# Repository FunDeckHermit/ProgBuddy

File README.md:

# ProgBuddy

ProgBuddy is a compact USB 2.0 hub and power-monitoring board designed for practical bench use and embedded USB debugging. It combines a high-side current sensing front end, USB PD passthrough switching, a web interface over USB CDC/NCM, and a small user-facing display for live system status.

## Features

- USB 2.0 hub function with configurable upstream/downstream swap capability
- Accurate current sensing for downstream ports and total hub current
- INA229-based voltage and energy monitoring
- USB PD passthrough with CC-line switching and port control
- Web interface exposed over USB communication device class (CDC/NCM)
- LCD display for live voltages, power, and status information
- Flexible board layout for USB upstream/downstream swapping and reconfiguration

## Design goals

This project is intended to make USB power and debugging data visible and controllable in a single tool. The board is useful for:

- measuring real-time current draw from USB devices
- validating USB PD behavior and pass-through routing
- monitoring port voltage and energy usage
- debugging USB device behavior from a simple web dashboard
- presenting live status on a local panel without needing a separate host tool

## Hardware overview

The system integrates several key functions:

- USB 2.0 hub switching and port routing
- accurate current measurement using dedicated sensing hardware
- bus voltage and energy calculations with the INA229
- USB-C PD passthrough handling with CC switching
- configurable USB upstream/downstream connection options
- local display and status indication

## Firmware and interface

The project exposes a browser-based interface over USB CDC/NCM, allowing inspection and control without a traditional serial adapter stack. This makes it convenient for lab, prototype, and dev-board workflows where a clean USB-connected control path is valuable.

## Typical use cases

- USB port power auditing
- USB device validation and debugging
- PD-aware hub testing
- Bench monitoring for USB-powered electronics
- Controlled power and signal routing in prototypes

## Notes

This repository contains the design files and project documentation for the hardware and embedded firmware work. The board is intended to be configurable and practical, with emphasis on measurement accuracy, USB signal integrity, and operational flexibility.

## Status

This project is an active hardware and firmware design, with emphasis on USB hub functionality, power monitoring, and USB PD passthrough behavior.

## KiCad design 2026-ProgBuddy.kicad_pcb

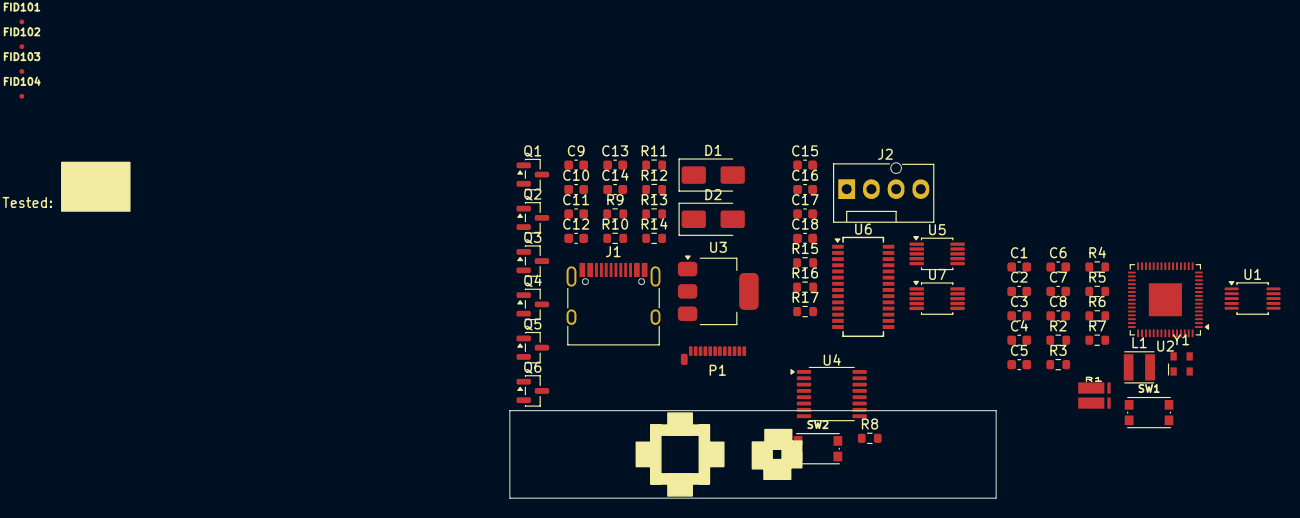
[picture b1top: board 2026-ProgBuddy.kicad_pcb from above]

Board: 4 copper layers, 50.0 x 9.0 mm, 61 parts (0 on the bottom side), 55 nets, no tracks yet.

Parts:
C1, C2, C11, C14: 100nF; C_0603_1608Metric
C3, C4, C5, C6, C7, C8, C9, C10, C12, C13, C15, C16, C17, C18: 2.2uF; C_0603_1608Metric
D1, D2: SS14; D_SMA
FID101, FID102, FID103, FID104: Fiducial; Fiducial_0.5mm_Mask1mm
J1: UJ20-C-H-C-4-SMT-TR; USB_C_Receptacle_SSKY_UJ20-C-H-C-4-SMT-TR
J2: Conn_01x04; FanPinHeader_1x04_P2.54mm_Vertical
L1: 3.3uH; L_Bourns-3015
P1: USB_C_Plug; USB_C_Plug_Molex_105444
Q1, Q2, Q4, Q6: Si2347DS; SOT-23
Q3, Q5: BSS316; SOT-23
R1: 33mR; R_Shunt_Susumu_1206
R2, R3: 68R; R_0603_1608Metric
R4, R5, R6: 33R; R_0603_1608Metric
R7, R8: 1K0; R_0603_1608Metric
R9, R10, R11, R12: 10K; R_0603_1608Metric
R13, R14: 5K1; R_0603_1608Metric
R15, R16, R17: 2K7; R_0603_1608Metric
SW1, SW2: KMR223GLFG; SW_Push_1P1T_NO_CK_KMR2
U1: INA229; TSSOP-10_3x3mm_P0.5mm
U2: RP2354A; QFN-60-1EP_7x7mm_P0.4mm_EP3.4x3.4mm
U3: TLV1117-33CDCYG3; SOT-223-3_TabPin2
U4: HEF4052BTT; TSSOP-16_4.4x5mm_P0.65mm
U5, U7: FSUSB42MUX; MSOP-10_3x3mm_P0.5mm
U6: FE1.1s; SSOP-28_3.9x9.9mm_P0.635mm
Y1: ASDMB-12.000MHz; Oscillator_SMD_Abracon_ASDMB-4Pin_2.5x2.0mm

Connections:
12MHz: U2.21 (XIN), U6.3 (XIN), Y1.3 (Out)
+1V1: C7.1, C8.1, L1.2, U2.6 (DVDD), U2.23 (DVDD), U2.39 (DVDD), U2.50 (VREG_FB)
+1V8: C17.1, C18.1, U6.12 (VD18_O), U6.28 (VD18)
+3.3V: C2.1, C5.1, C6.1, C12.1, C13.1, C14.1, C15.1, C16.1, R4.1, R16.1, R17.1, U1.6 (VS), U2.1 (IOVDD), U2.11 (IOVDD), U2.20 (IOVDD), U2.30 (IOVDD), U2.38 (IOVDD), U2.44 (ADC_AVDD), U2.45 (IOVDD), U2.49 (VREG_VIN), U2.53 (USB_OTP_VDD), U2.54 (QSPI_IOVDD), U3.2 (VO), U4.11 (1Y3), U5.1 (VCC), U6.13 (VD33), U6.18 (VBUSM), U6.19 (BUSJ), U6.21 (VD33_O), U7.1 (VCC), Y1.4 (VDD)
+5C: D2.2 (A), P1.A4 (VBUS), P1.A9 (VBUS), P1.B4 (VBUS), P1.B9 (VBUS), Q2.3 (D), U4.15 (1Y2)
+5F: D1.2 (A), J1.A4 (VBUS), J1.A9 (VBUS), J1.B4 (VBUS), J1.B9 (VBUS), Q4.3 (D), U4.14 (1Y1)
+5VD: C9.1, C10.1, C11.1, D1.1 (K), D2.1 (K), U3.3 (VI), U4.6 (~E), U4.16 (VDD)
D+_{1}: J1.A6 (D+), J1.B6 (D+), U5.9 (HSD2+), U7.9 (HSD2+)
D+_{2}: P1.A6 (D+), U5.7 (HSD1+), U7.7 (HSD1+)
D-_{1}: J1.A7 (D-), J1.B7 (D-), U5.8 (HSD2-), U7.8 (HSD2-)
D-_{2}: P1.A7 (D-), U5.6 (HSD1-), U7.6 (HSD1-)
EN_Down: Q3.1 (G), R10.1, U2.27 (GPIO16)
EN_Up: Q5.1 (G), R11.1, U2.28 (GPIO17)
GND: C2.2, C3.2, C4.2, C5.2, C6.2, C7.2, C8.2, C9.2, C10.2, C11.2, C12.2, C13.2, C14.2, C15.2, C16.2, C17.2, C18.2, J1.A1 (GND), J1.A12 (GND), J1.B1 (GND), J1.B12 (GND), J1.S1 (SHIELD), J2.4, P1.A1 (GND), P1.A12 (GND), P1.B1 (GND), P1.B12 (GND), P1.SH (SHIELD), Q3.2 (S), Q5.2 (S), R7.2, R8.2, R10.2, R11.2, R13.2, R14.2, R15.2, U1.1 (~CS), U1.7 (GND), U2.47 (VREG_PGND), U2.61 (GND), U3.1 (GND), U4.7 (VEE), U4.8 (VSS), U5.5 (GND), U6.1 (VSS), U7.5 (GND), Y1.2 (GND)
unnamed: J1.A5 (CC1), R14.1
unnamed: J1.B5 (CC2), R13.1
unnamed: J2.2, U6.7 (DP3)
unnamed: J2.3, U6.6 (DM3)
unnamed: Q1.3 (D), R1.1
unnamed: Q1.1 (G), Q2.1 (G), Q3.3 (D), R9.2
unnamed: Q1.2 (S), Q2.2 (S), R9.1
unnamed: Q4.1 (G), Q5.3 (D), Q6.1 (G), R12.2
unnamed: Q4.2 (S), Q6.2 (S), R12.1
unnamed: Q6.3 (D), R1.4
unnamed: R7.1, SW1.1
unnamed: R8.1, SW2.1
unnamed: C1.1, R3.2, U1.10 (IN+)
unnamed: C1.2, R2.2, U1.9 (IN-)
unnamed: U1.4 (MISO), U2.12 (GPIO8)
unnamed: U1.2 (MOSI), U2.14 (GPIO10)
unnamed: U1.5 (SCLK), U2.10 (GPIO7)
unnamed: U1.8 (VBUS), U4.13 (1Z)
unnamed: U1.3 (~ALERT), U2.13 (GPIO9)
unnamed: SW1.2, U2.26 (RUN)
unnamed: R5.2, U2.51 (USB_DM)
unnamed: R6.2, U2.52 (USB_DP)
unnamed: C3.1, C4.1, R4.2, U2.46 (VREG_AVDD)
unnamed: L1.1, U2.48 (VREG_LX)
unnamed: SW2.2, U2.60 (~QSPI_SS)
unnamed: U5.3 (D+), U6.11 (DP1)
unnamed: U5.4 (D-), U6.10 (DM1)
unnamed: U6.15 (DMU), U7.4 (D-)
unnamed: U6.16 (DPU), U7.3 (D+)
unnamed: R15.1, U6.14 (REXT)
RP_USB+: R6.1, U6.9 (DP2)
RP_USB-: R5.1, U6.8 (DM2)
SEL_{USB1}: U2.33 (GPIO21), U5.2 (SEL)
SEL_{USB2}: U2.34 (GPIO22), U7.2 (SEL)
Shunt+: J2.1, R1.3, R3.1, U4.12 (1Y0)
Shunt-: R1.2, R2.1
VBUS_{SEL1}: U2.2 (GPIO0), U4.10 (S1)
VBUS_{SEL2}: U2.3 (GPIO1), U4.9 (S2)
~EN_{USB}: U2.32 (GPIO20), U5.10 (~OE), U7.10 (~OE)
~OVC_{USB}: R17.2, U2.31 (GPIO19), U6.26 (OVCJ)
~RST_{HUB}: R16.2, U2.35 (GPIO23), U6.17 (~XRSTJ)

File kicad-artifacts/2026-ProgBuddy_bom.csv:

"Designator"," Comment"," MPN"," Footprint"," Quantity"
"C1,C2,C11,C14","100nF","AS0603KRX7R0BB104","Capacitor_SMD:C_0603_1608Metric","4"
"C3,C4,C5,C6,C7,C8,C9,C10,C12,C13,C15,C16,C17,C18","2.2uF","0603B225K100CT","Capacitor_SMD:C_0603_1608Metric","14"
"D1,D2","SS14","","Diode_SMD:D_SMA","2"
"F1","200mA","0ZCH0020FF2E","Fuse:Fuse_1210_3225Metric_Pad1.42x2.65mm_HandSolder","1"
"J1","UJ20-C-H-C-4-SMT-TR","UJ20-C-H-C-4-SMT-TR","0_NRD_footprints:USB_C_Receptacle_SSKY_UJ20-C-H-C-4-SMT-TR","1"
"J2","Conn_01x04","","Connector:FanPinHeader_1x04_P2.54mm_Vertical","1"
"L1","3.3uH","SRN3015-3R3M","0_NRD_footprints:L_Bourns-3015","1"
"P1","USB_C_Plug","","Connector_USB:USB_C_Plug_Molex_105444","1"
"Q1,Q2,Q4,Q6","Si2347DS","","Package_TO_SOT_SMD:SOT-23","4"
"Q3,Q5","BSS316","BSS316NH6327XTSA1","Package_TO_SOT_SMD:SOT-23","2"
"R1","33mR","KRL3216T4A-M-R033-F-T1 ","0_NRD_footprints:R_Shunt_Susumu_1206","1"
"R2,R3","68R","RC0603FR-0768RL","Resistor_SMD:R_0603_1608Metric","2"
"R4,R5,R6","33R","RC0603FR-0733RL","Resistor_SMD:R_0603_1608Metric","3"
"R7,R8","1K0","RC0603FR-07FRE131KL","Resistor_SMD:R_0603_1608Metric","2"
"R9,R10,R11,R12,R18","10K","RC0603FR-0710KL","Resistor_SMD:R_0603_1608Metric","5"
"R13,R14","5K1","RC0603FR-075K1L","Resistor_SMD:R_0603_1608Metric","2"
"R15,R16,R17","2K7","RC0603FR-072K7L","Resistor_SMD:R_0603_1608Metric","3"
"SW1,SW2","KMR223GLFG","KMR223GLFG","0_NRD_footprints:SW_Push_1P1T_NO_CK_KMR2","2"
"TP1,TP2,TP3,TP4","TestPoint_Square","","TestPoint:TestPoint_THTPad_1.0x1.0mm_Drill0.5mm","4"
"U1","INA229","","Package_SO:TSSOP-10_3x3mm_P0.5mm","1"
"U2","RP2354A","","Package_DFN_QFN:QFN-60-1EP_7x7mm_P0.4mm_EP3.4x3.4mm","1"
"U4","TLF80511TFV33","TLF80511TFV33","Package_TO_SOT_SMD:TO-252-2","1"
"U5,U7,U8,U9","FSUSB42MUX","","Package_SO:MSOP-10_3x3mm_P0.5mm","4"
"U6","FE1.1s","","Package_SO:SSOP-28_3.9x9.9mm_P0.635mm","1"
"Y1","ASDMB-12.000MHz","","Oscillator:Oscillator_SMD_Abracon_ASDMB-4Pin_2.5x2.0mm","1"
